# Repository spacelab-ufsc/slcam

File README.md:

<h1 align="center">
    SLCam
    <br>
</h1>

<h4 align="center">Camera payload designed and developed by SpaceLab.</h4>

<p align="center">

</p>

<p align="center">
    <a href="#overview">Overview</a> •
    <a href="#repository-organization">Repository Organizarion</a> •
    <a href="#releases">Releases</a> •
    <a href="#notes">Notes</a>
</p>

## Overview

The SLCam ("SpaceLab Camera") is a camera payload designed to be used in nanosatellite missions. The main object is to take pictures of the Earth from space. It's the first project from SpaceLab using cameras in payloads.

## Repository Organization

* docs: Technical documentation (including firmware, hardware, user guide, and datasheet).
* firmware: Firmware project (sources and configs).
* hardware: Hardware project (sources and outputs).
* mechanical: Mechanical project (sources and outputs).
* software: Software to communicate with the camera (sources).

## License

This project is open-source under three different licenses: GNU General Public License v3.0 for firmware sources, CERN Open Hardware License v2.0 for hardware and mechanical files, and CC BY-SA 4.0 for the documentation. Some third-part files and libraries are subjected to their specific terms and licenses.

## Releases

The SLCam software and hardware releases are synchronized in order to garantee compatibility. Then, using diferent versions might lead to unpredictable behavior. Refer to the [documentation](https://github.com/spacelab-ufsc/slcam/tree/main/doc) for compatibility notes.

## Notes

More info about the SpaceLab: [GitHub](https://github.com/spacelab-ufsc/spacelab) and [Website](https://spacelab.ufsc.br/en/home/).

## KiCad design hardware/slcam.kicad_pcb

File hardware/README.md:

<h1 align="center">
    SLCAM HARDWARE PROJECT
    <br>
</h1>

<h4 align="center">Hardware project of the SLCam module.</h4>

<p align="center">

</p>

<p align="center">
    <a href="#overview">Overview</a> •
    <a href="#bd">Block Diagram</a> •
    <a href="#license">License</a>
</p>

## Overview

The hardware project of the SpaceLab camera is composed by the PCB of the controller module.

## Block Diagram

The block diagram of the controller PCB can be seen below:

## License

This repository containing hardware files is licensed under CERN Open Hardware License, version 2.

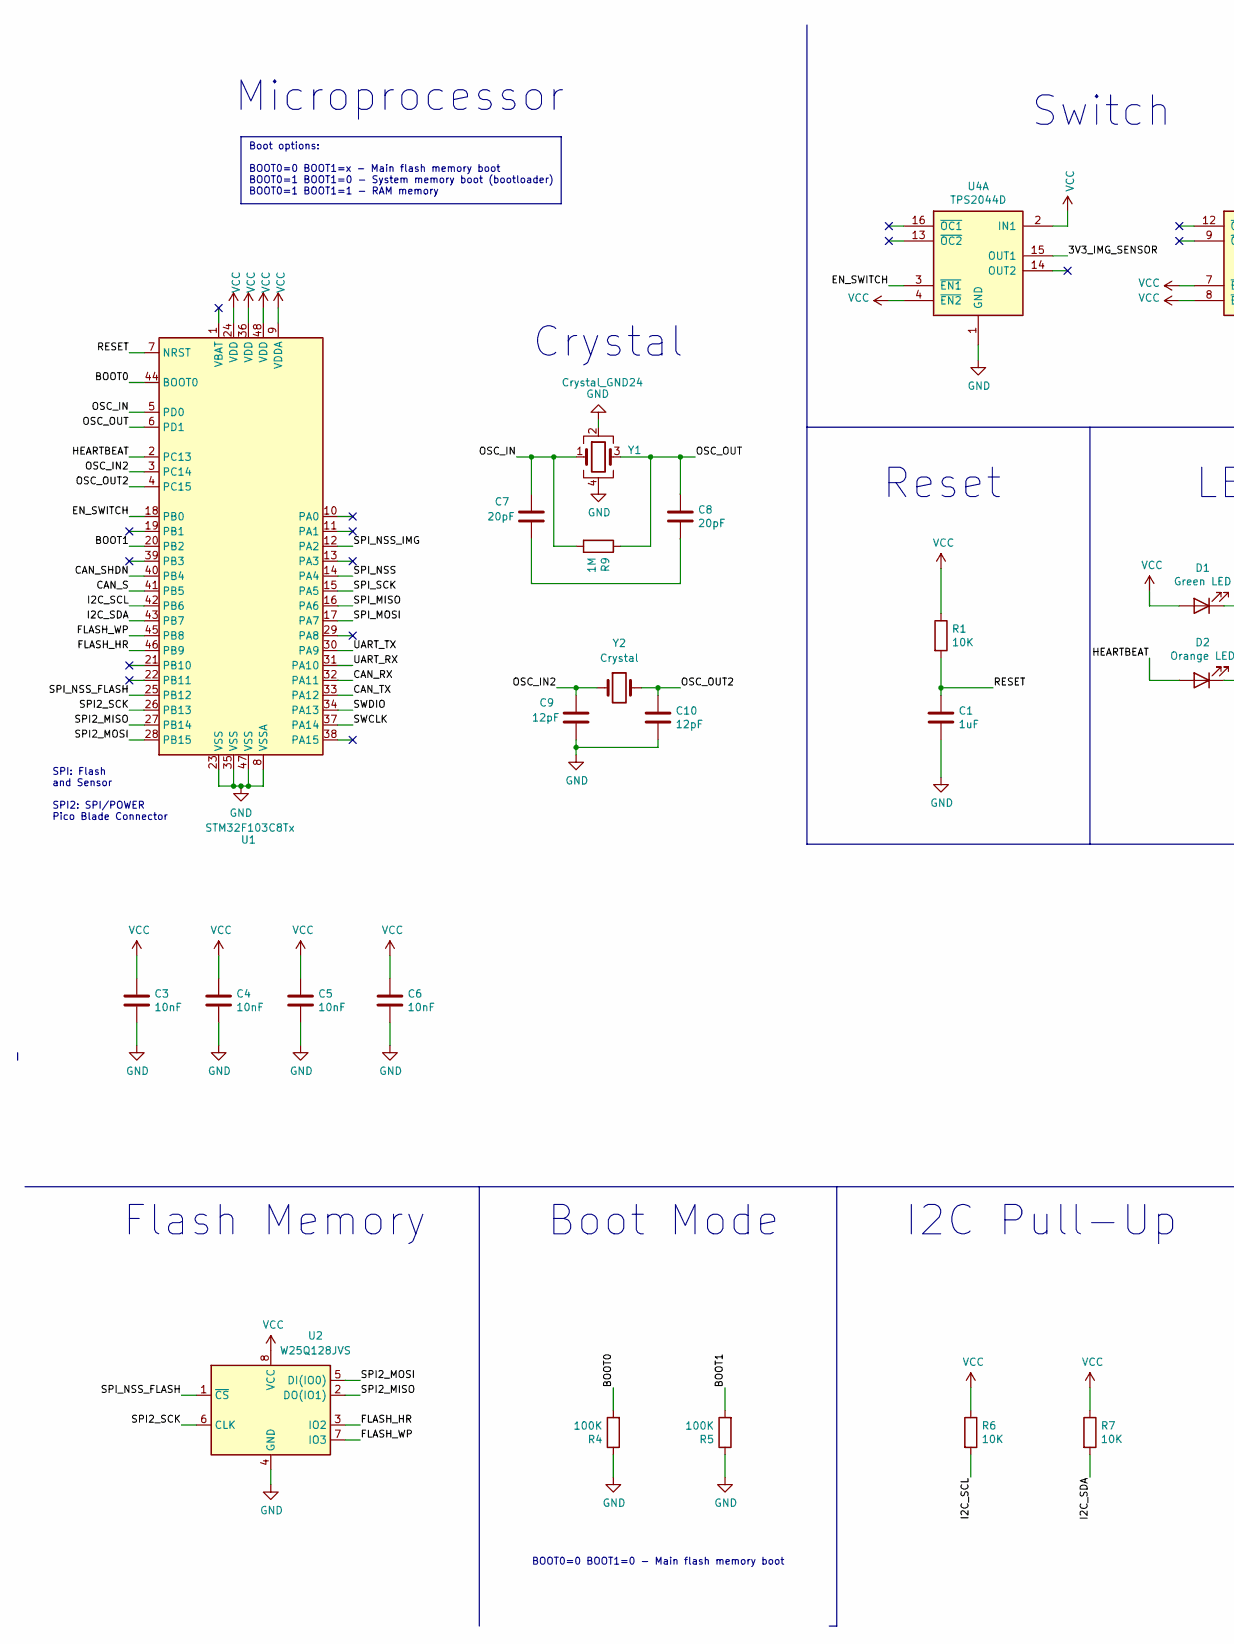
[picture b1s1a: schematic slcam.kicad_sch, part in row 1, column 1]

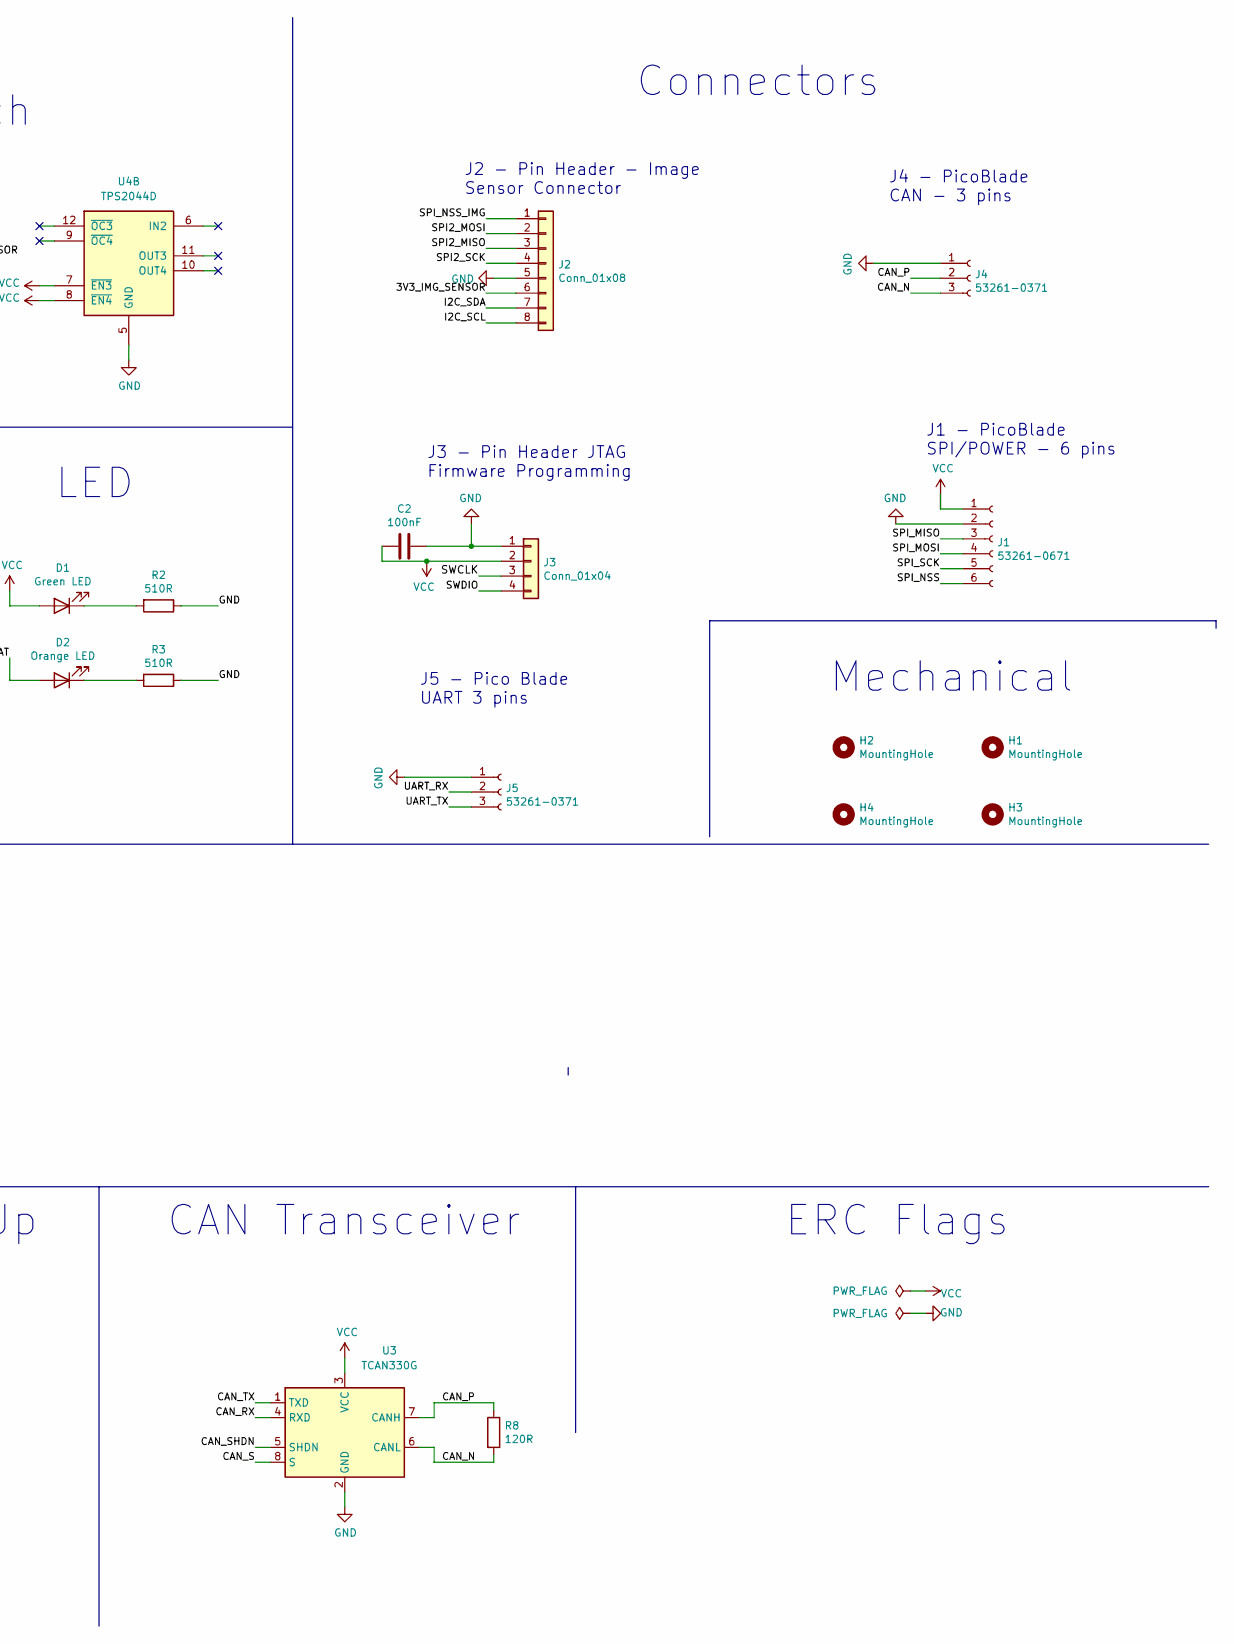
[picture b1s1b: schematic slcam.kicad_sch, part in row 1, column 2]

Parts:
C1: 1uF; C_0603_1608Metric_Pad1.05x0.95mm_HandSolder; Partnumber GCJ188R71E105KA01D
C2: 100nF; C_0603_1608Metric_Pad1.05x0.95mm_HandSolder; Partnumber C0603C104K5RAC3121
C3, C4, C5, C6: 10nF; C_0603_1608Metric_Pad1.05x0.95mm_HandSolder; Partnumber VJ0603Y103KXJAC31X
C7, C8: 20pF; C_0603_1608Metric_Pad1.05x0.95mm_HandSolder; Partnumber CBR06C200J5GACAUTO
C9, C10: 12pF; C_0603_1608Metric_Pad1.08x0.95mm_HandSolder; Partnumber CL21C120FBANNNC
D1: Green LED; LED_0603_1608Metric_Pad1.05x0.95mm_HandSolder; Partnumber 150060VS75003
D2: Orange LED; LED_0603_1608Metric_Pad1.05x0.95mm_HandSolder; Partnumber CSL1901DW1
H1, H2, H3, H4: MountingHole; MountingHole_3.2mm_M3_Pad
J1: 53261-0671; Molex_PicoBlade_53261-0671_1x06-1MP_P1.25mm_Horizontal; Partnumber 53261-0671
J2: Conn_01x08; PinHeader_1x08_P2.54mm_Vertical; Partnumber SSQ-108-03-G-S
J3: Conn_01x04; PinHeader_1x04_P2.54mm_Vertical; Partnumber 5-146305-4
J4, J5: 53261-0371; Molex_PicoBlade_53261-0371_1x03-1MP_P1.25mm_Horizontal; Partnumber 53261-0371
R1, R6, R7: 10K; R_0603_1608Metric_Pad1.05x0.95mm_HandSolder; Partnumber MCT06030C1002FP500
R2, R3: 510R; R_0603_1608Metric_Pad1.05x0.95mm_HandSolder; Partnumber MCT06030C5100FP500
R4, R5: 100K; R_0603_1608Metric_Pad1.05x0.95mm_HandSolder; Partnumber MCT0603MC1003FP500
R8: 120R; R_0603_1608Metric_Pad1.05x0.95mm_HandSolder; Partnumber MCT06030C1200FP500
R9: 1M; R_0603_1608Metric_Pad1.05x0.95mm_HandSolder; Partnumber MCT06030C1004FP500
U1: STM32F103C8Tx; LQFP-48_7x7mm_P0.5mm; Partnumber STM32F103C8T6
U2: W25Q128JVS; SOIC-8_5.23x5.23mm_P1.27mm; Partnumber W25Q128JVSIM TR
U3: TCAN330G; SOIC-8_3.9x4.9mm_P1.27mm; Partnumber TCAN330GD
U4: TPS2044D; SOIC-16_3.9x9.9mm_P1.27mm; Partnumber TPS2044D
Y1: Crystal_GND24; Crystal_SMD_Abracon_ABM8G-4Pin_3.2x2.5mm; Partnumber ECS-80-10-33-CHN-TR3
Y2: Crystal; Crystal_SMD_MicroCrystal_CC7V-T1A-2Pin_3.2x1.5mm_HandSolder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; Partnumber ECS-.327-12.5-34S-TR

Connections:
/3V3_IMG_SENSOR: J2.6, U4.15 (OUT1)
/BOOT0: R4.2, U1.44 (BOOT0)
/BOOT1: R5.2, U1.20 (PB2)
/CAN_N: J4.3, R8.2, U3.6 (CANL)
/CAN_P: J4.2, R8.1, U3.7 (CANH)
/CAN_RX: U1.32 (PA11), U3.4 (RXD)
/CAN_S: U1.41 (PB5), U3.8 (S)
/CAN_SHDN: U1.40 (PB4), U3.5 (SHDN)
/CAN_TX: U1.33 (PA12), U3.1 (TXD)
/EN_SWITCH: U1.18 (PB0), U4.3 (~EN1)
/FLASH_HR: U1.46 (PB9), U2.3 (IO2)
/FLASH_WP: U1.45 (PB8), U2.7 (IO3)
/HEARTBEAT: D2.2 (A), U1.2 (PC13)
/I2C_SCL: J2.8, R6.2, U1.42 (PB6)
/I2C_SDA: J2.7, R7.2, U1.43 (PB7)
/OSC_IN: C7.1, R9.2, U1.5 (PD0), Y1.1
/OSC_IN2: C9.1, U1.3 (PC14), Y2.1
/OSC_OUT: C8.1, R9.1, U1.6 (PD1), Y1.3
/OSC_OUT2: C10.1, U1.4 (PC15), Y2.2
/RESET: C1.1, R1.2, U1.7 (NRST)
/SPI2_MISO: J2.3, U1.27 (PB14), U2.2 (DO(IO1))
/SPI2_MOSI: J2.2, U1.28 (PB15), U2.5 (DI(IO0))
/SPI2_SCK: J2.4, U1.26 (PB13), U2.6 (CLK)
/SPI_MISO: J1.3, U1.16 (PA6)
/SPI_MOSI: J1.4, U1.17 (PA7)
/SPI_NSS: J1.6, U1.14 (PA4)
/SPI_NSS_FLASH: U1.25 (PB12), U2.1 (~CS)
/SPI_NSS_IMG: J2.1, U1.12 (PA2)
/SPI_SCK: J1.5, U1.15 (PA5)
/SWCLK: J3.3, U1.37 (PA14)
/SWDIO: J3.4, U1.34 (PA13)
/UART_RX: J5.2, U1.31 (PA10)
/UART_TX: J5.3, U1.30 (PA9)
GND: C1.2, C2.1, C3.2, C4.2, C5.2, C6.2, C9.2, C10.2, J1.2, J2.5, J3.1, J4.1, J5.1, R2.1, R3.1, R4.1, R5.1, U1.8 (VSSA), U1.23 (VSS), U1.35 (VSS), U1.47 (VSS), U2.4 (GND), U3.2 (GND), U4.1 (GND), U4.5 (GND), Y1.2, Y1.4
unnamed: C7.2, C8.2
unnamed: D1.1 (K), R2.2
unnamed: D2.1 (K), R3.2
VCC: C2.2, C3.1, C4.1, C5.1, C6.1, D1.2 (A), J1.1, J3.2, R1.1, R6.1, R7.1, U1.9 (VDDA), U1.24 (VDD), U1.36 (VDD), U1.48 (VDD), U2.8 (VCC), U3.3 (VCC), U4.2 (IN1), U4.4 (~EN2), U4.7 (~EN3), U4.8 (~EN4)

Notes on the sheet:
ERC Flags
Boot options: BOOT0=0 BOOT1=x - Main flash memory boot BOOT0=1 BOOT1=0 - System memory boot (bootloader) BOOT0=1 BOOT1=1 - RAM memory
Mechanical
J3 - Pin Header JTAG Firmware Programming
Switch
J1 - PicoBlade SPI/POWER - 6 pins
LED
J4 - PicoBlade CAN - 3 pins
Boot Mode
BOOT0=0 BOOT1=0 - Main flash memory boot
Connectors
J5 - Pico Blade UART 3 pins
J2 - Pin Header - Image Sensor Connector
Flash Memory
CAN Transceiver
SPI: Flash and Sensor SPI2: SPI/POWER Pico Blade Connector
Microprocessor
Reset
I2C Pull-Up
Crystal

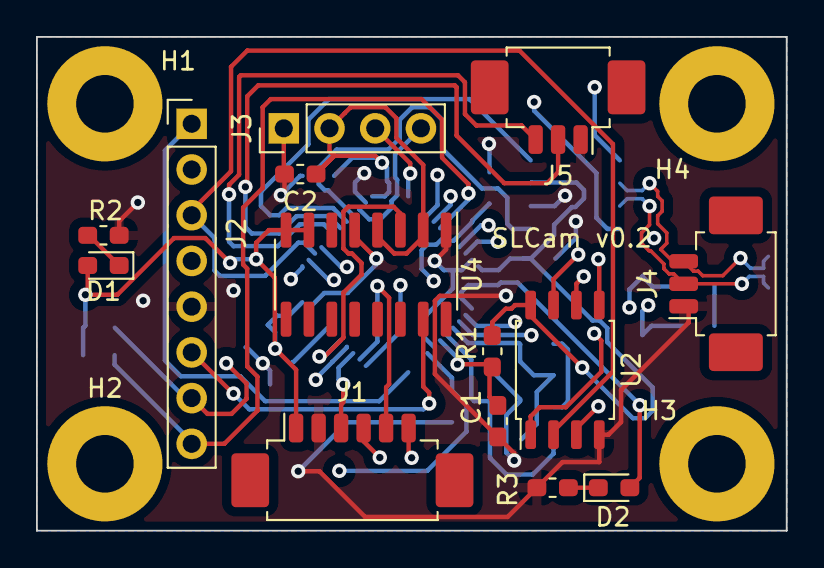
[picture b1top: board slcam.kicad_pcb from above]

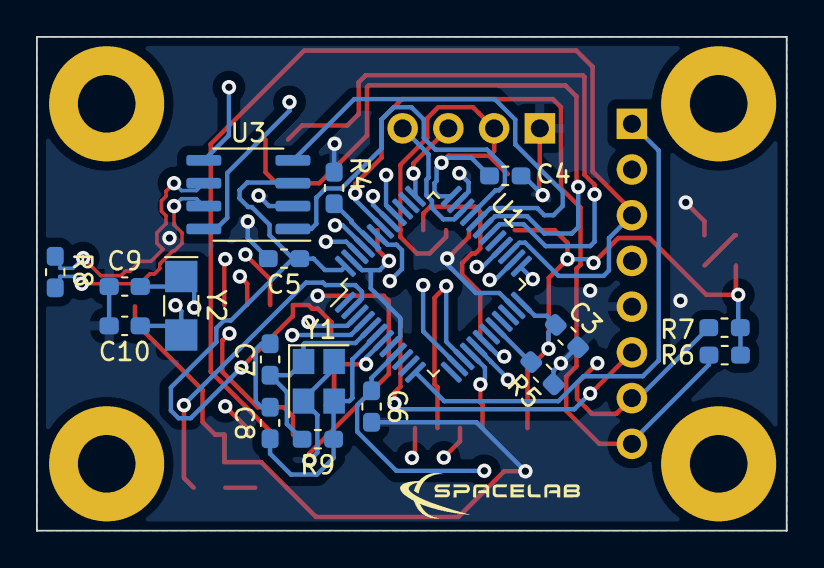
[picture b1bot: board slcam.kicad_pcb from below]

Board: 4 copper layers, 41.7 x 27.4 mm, 36 parts (18 on the bottom side), 38 nets.

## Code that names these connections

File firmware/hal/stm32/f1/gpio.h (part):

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/* Default alternate functions of some pins (with and without remapping) */

/* CAN1 / CAN GPIO */
#define GPIO_CAN1_RX			GPIO11		/* PA11 */
#define GPIO_CAN1_TX			GPIO12		/* PA12 */
#define GPIO_CAN_RX			GPIO_CAN1_RX	/* Alias */
#define GPIO_CAN_TX			GPIO_CAN1_TX	/* Alias */

#define GPIO_CAN_PB_RX			GPIO8		/* PB8 */
#define GPIO_CAN_PB_TX			GPIO9		/* PB9 */
#define GPIO_CAN1_PB_RX			GPIO_CAN_PB_RX	/* Alias */
#define GPIO_CAN1_PB_TX			GPIO_CAN_PB_TX	/* Alias */

#define GPIO_CAN_PD_RX			GPIO0		/* PD0 */
#define GPIO_CAN_PD_TX			GPIO1		/* PD1 */
#define GPIO_CAN1_PD_RX			GPIO_CAN_PD_RX	/* Alias */
#define GPIO_CAN1_PD_TX			GPIO_CAN_PD_TX	/* Alias */

/* CAN1 / CAN BANK */
#define GPIO_BANK_CAN1_RX		GPIOA		/* PA11 */
#define GPIO_BANK_CAN1_TX		GPIOA		/* PA12 */
#define GPIO_BANK_CAN_RX		GPIO_BANK_CAN1_RX /* Alias */
#define GPIO_BANK_CAN_TX		GPIO_BANK_CAN1_TX /* Alias */

#define GPIO_BANK_CAN_PB_RX		GPIOB		/* PB8 */
#define GPIO_BANK_CAN_PB_TX		GPIOB		/* PB9 */
#define GPIO_BANK_CAN1_PB_RX		GPIO_BANK_CAN_PB_RX /* Alias */
#define GPIO_BANK_CAN1_PB_TX		GPIO_BANK_CAN_PB_TX /* Alias */

#define GPIO_BANK_CAN_PD_RX		GPIOD		/* PD0 */
#define GPIO_BANK_CAN_PD_TX		GPIOD		/* PD1 */
#define GPIO_BANK_CAN1_PD_RX		GPIO_BANK_CAN_PD_RX /* Alias */
#define GPIO_BANK_CAN1_PD_TX		GPIO_BANK_CAN_PD_TX /* Alias */

/* CAN2 GPIO */
#define GPIO_CAN2_RX			GPIO12		/* PB12 */
#define GPIO_CAN2_TX			GPIO13		/* PB13 */

#define GPIO_CAN2_RE_RX			GPIO5		/* PB5 */
#define GPIO_CAN2_RE_TX			GPIO6		/* PB6 */

/* CAN2 BANK */
#define GPIO_BANK_CAN2_RX		GPIOB		/* PB12 */
#define GPIO_BANK_CAN2_TX		GPIOB		/* PB13 */

#define GPIO_BANK_CAN2_RE_RX		GPIOB		/* PB5 */
#define GPIO_BANK_CAN2_RE_TX		GPIOB		/* PB6 */

/* JTAG/SWD GPIO */
#define GPIO_JTMS_SWDIO			GPIO13		/* PA13 */
#define GPIO_JTCK_SWCLK			GPIO14		/* PA14 */
#define GPIO_JTDI			GPIO15		/* PA15 */
#define GPIO_JTDO_TRACESWO		GPIO3		/* PB3 */
#define GPIO_JNTRST			GPIO4		/* PB4 */
#define GPIO_TRACECK			GPIO2		/* PE2 */
#define GPIO_TRACED0			GPIO3		/* PE3 */
#define GPIO_TRACED1			GPIO4		/* PE4 */
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#define GPIO_TRACED3			GPIO6		/* PE6 */

/* JTAG/SWD BANK */
#define GPIO_BANK_JTMS_SWDIO		GPIOA		/* PA13 */
#define GPIO_BANK_JTCK_SWCLK		GPIOA		/* PA14 */
#define GPIO_BANK_JTDI			GPIOA		/* PA15 */
#define GPIO_BANK_JTDO_TRACESWO		GPIOB		/* PB3 */
#define GPIO_BANK_JNTRST		GPIOB		/* PB4 */
#define GPIO_BANK_TRACECK		GPIOE		/* PE2 */
#define GPIO_BANK_TRACED0		GPIOE		/* PE3 */
#define GPIO_BANK_TRACED1		GPIOE		/* PE4 */
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/* Timer5 GPIO */
#define GPIO_TIM5_CH1			GPIO0		/* PA0 */
#define GPIO_TIM5_CH2			GPIO1		/* PA1 */
#define GPIO_TIM5_CH3			GPIO2		/* PA2 */
#define GPIO_TIM5_CH4			GPIO3		/* PA3 */

/* Timer5 BANK */
#define GPIO_BANK_TIM5_CH1		GPIOA		/* PA0 */
#define GPIO_BANK_TIM5_CH2		GPIOA		/* PA1 */
#define GPIO_BANK_TIM5_CH3		GPIOA		/* PA2 */
#define GPIO_BANK_TIM5_CH4		GPIOA		/* PA3 */
#define GPIO_BANK_TIM5			GPIOA

/* Timer4 GPIO */
#define GPIO_TIM4_CH1			GPIO6		/* PB6 */
#define GPIO_TIM4_CH2			GPIO7		/* PB7 */
#define GPIO_TIM4_CH3			GPIO8		/* PB8 */
#define GPIO_TIM4_CH4			GPIO9		/* PB9 */

#define GPIO_TIM4_RE_CH1		GPIO12		/* PD12 */
#define GPIO_TIM4_RE_CH2		GPIO13		/* PD13 */
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#define GPIO_TIM4_RE_CH4		GPIO15		/* PD15 */

/* Timer4 BANK */
#define GPIO_BANK_TIM4_CH1		GPIOB		/* PB6 */
#define GPIO_BANK_TIM4_CH2		GPIOB		/* PB7 */
#define GPIO_BANK_TIM4_CH3		GPIOB		/* PB8 */
#define GPIO_BANK_TIM4_CH4		GPIOB		/* PB9 */
#define GPIO_BANK_TIM4			GPIOB

#define GPIO_BANK_TIM4_RE_CH1		GPIOD		/* PD12 */
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#define GPIO_BANK_TIM4_RE		GPIOD

/* Timer3 GPIO */
#define GPIO_TIM3_CH1			GPIO6		/* PA6 */
#define GPIO_TIM3_CH2			GPIO7		/* PA7 */
#define GPIO_TIM3_CH3			GPIO0		/* PB0 */
#define GPIO_TIM3_CH4			GPIO1		/* PB1 */

#define GPIO_TIM3_PR_CH1		GPIO4		/* PB4 */
#define GPIO_TIM3_PR_CH2		GPIO5		/* PB5 */
#define GPIO_TIM3_PR_CH3		GPIO0		/* PB0 */
#define GPIO_TIM3_PR_CH4		GPIO1		/* PB1 */

#define GPIO_TIM3_FR_CH1		GPIO6		/* PC6 */
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#define GPIO_TIM3_FR_CH4		GPIO9		/* PC9 */

/* Timer3 BANK */
#define GPIO_BANK_TIM3_CH1		GPIOA		/* PA6 */
#define GPIO_BANK_TIM3_CH2		GPIOA		/* PA7 */
#define GPIO_BANK_TIM3_CH3		GPIOB		/* PB0 */
#define GPIO_BANK_TIM3_CH4		GPIOB		/* PB1 */
#define GPIO_BANK_TIM3_CH12		GPIOA
#define GPIO_BANK_TIM3_CH34		GPIOB

#define GPIO_BANK_TIM3_PR_CH1		GPIOB		/* PB4 */
#define GPIO_BANK_TIM3_PR_CH2		GPIOB		/* PB5 */
#define GPIO_BANK_TIM3_PR_CH3		GPIOB		/* PB0 */
#define GPIO_BANK_TIM3_PR_CH4		GPIOB		/* PB1 */
#define GPIO_BANK_TIM3_PR		GPIOB

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/* Timer2 GPIO */
#define GPIO_TIM2_CH1_ETR		GPIO0		/* PA0 */
#define GPIO_TIM2_CH2			GPIO1		/* PA1 */
#define GPIO_TIM2_CH3			GPIO2		/* PA2 */
#define GPIO_TIM2_CH4			GPIO3		/* PA3 */

#define GPIO_TIM2_PR1_CH1_ETR		GPIO15		/* PA15 */
#define GPIO_TIM2_PR1_CH2		GPIO3		/* PB3 */
#define GPIO_TIM2_PR1_CH3		GPIO2		/* PA2 */
#define GPIO_TIM2_PR1_CH4		GPIO3		/* PA3 */

#define GPIO_TIM2_PR2_CH1_ETR		GPIO0		/* PA0 */
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/* Timer2 BANK */
#define GPIO_BANK_TIM2_CH1_ETR		GPIOA		/* PA0 */
#define GPIO_BANK_TIM2_CH2		GPIOA		/* PA1 */
#define GPIO_BANK_TIM2_CH3		GPIOA		/* PA2 */
#define GPIO_BANK_TIM2_CH4		GPIOA		/* PA3 */
#define GPIO_BANK_TIM2			GPIOA

#define GPIO_BANK_TIM2_PR1_CH1_ETR	GPIOA		/* PA15 */
#define GPIO_BANK_TIM2_PR1_CH2		GPIOB		/* PB3 */
#define GPIO_BANK_TIM2_PR1_CH3		GPIOA		/* PA2 */
#define GPIO_BANK_TIM2_PR1_CH4		GPIOA		/* PA3 */
#define GPIO_BANK_TIM2_PR1_CH134	GPIOA

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#define GPIO_BANK_TIM2_FR_CH234		GPIOB

/* Timer1 GPIO */
#define GPIO_TIM1_ETR			GPIO12		/* PA12 */
#define GPIO_TIM1_CH1			GPIO8		/* PA8 */
#define GPIO_TIM1_CH2			GPIO9		/* PA9 */
#define GPIO_TIM1_CH3			GPIO10		/* PA10 */
#define GPIO_TIM1_CH4			GPIO11		/* PA11 */
#define GPIO_TIM1_BKIN			GPIO12		/* PB12 */
#define GPIO_TIM1_CH1N			GPIO13		/* PB13 */
#define GPIO_TIM1_CH2N			GPIO14		/* PB14 */
#define GPIO_TIM1_CH3N			GPIO15		/* PB15 */

#define GPIO_TIM1_PR_ETR		GPIO12		/* PA12 */
#define GPIO_TIM1_PR_CH1		GPIO8		/* PA8 */
#define GPIO_TIM1_PR_CH2		GPIO9		/* PA9 */
#define GPIO_TIM1_PR_CH3		GPIO10		/* PA10 */
#define GPIO_TIM1_PR_CH4		GPIO11		/* PA11 */
#define GPIO_TIM1_PR_BKIN		GPIO6		/* PA6 */
#define GPIO_TIM1_PR_CH1N		GPIO7		/* PA7 */
#define GPIO_TIM1_PR_CH2N		GPIO0		/* PB0 */
#define GPIO_TIM1_PR_CH3N		GPIO1		/* PB1 */

#define GPIO_TIM1_FR_ETR		GPIO7		/* PE7 */
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#define GPIO_TIM1_FR_CH3N		GPIO12		/* PE12 */

/* Timer1 BANK */
#define GPIO_BANK_TIM1_ETR		GPIOA		/* PA12 */
#define GPIO_BANK_TIM1_CH1		GPIOA		/* PA8 */
#define GPIO_BANK_TIM1_CH2		GPIOA		/* PA9 */
#define GPIO_BANK_TIM1_CH3		GPIOA		/* PA10 */
#define GPIO_BANK_TIM1_CH4		GPIOA		/* PA11 */
#define GPIO_BANK_TIM1_BKIN		GPIOB		/* PB12 */
#define GPIO_BANK_TIM1_CH1N		GPIOB		/* PB13 */
#define GPIO_BANK_TIM1_CH2N		GPIOB		/* PB14 */
#define GPIO_BANK_TIM1_CH3N		GPIOB		/* PB15 */
#define GPIO_BANK_TIM1_ETR_CH1234	GPIOA
#define GPIO_BANK_TIM1_BKIN_CH123N	GPIOB

#define GPIO_BANK_TIM1_PR_ETR		GPIOA		/* PA12 */
#define GPIO_BANK_TIM1_PR_CH1		GPIOA		/* PA8 */
#define GPIO_BANK_TIM1_PR_CH2		GPIOA		/* PA9 */
#define GPIO_BANK_TIM1_PR_CH3		GPIOA		/* PA10 */
#define GPIO_BANK_TIM1_PR_CH4		GPIOA		/* PA11 */
#define GPIO_BANK_TIM1_PR_BKIN		GPIOA		/* PA6 */
#define GPIO_BANK_TIM1_PR_CH1N		GPIOA		/* PA7 */
#define GPIO_BANK_TIM1_PR_CH2N		GPIOB		/* PB0 */
#define GPIO_BANK_TIM1_PR_CH3N		GPIOB		/* PB1 */
#define GPIO_BANK_TIM1_PR_ETR_CH1234_BKIN_CH1N	GPIOA
#define GPIO_BANK_TIM1_PR_CH23N		GPIOB
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/* USART3 GPIO */
#define GPIO_USART3_TX			GPIO10		/* PB10 */
#define GPIO_USART3_RX			GPIO11		/* PB11 */
#define GPIO_USART3_CK			GPIO12		/* PB12 */
#define GPIO_USART3_CTS			GPIO13		/* PB13 */
#define GPIO_USART3_RTS			GPIO14		/* PB14 */

#define GPIO_USART3_PR_TX		GPIO10		/* PC10 */
#define GPIO_USART3_PR_RX		GPIO11		/* PC11 */
#define GPIO_USART3_PR_CK		GPIO12		/* PC12 */
#define GPIO_USART3_PR_CTS		GPIO13		/* PB13 */
#define GPIO_USART3_PR_RTS		GPIO14		/* PB14 */

#define GPIO_USART3_FR_TX		GPIO8		/* PD8 */
#define GPIO_USART3_FR_RX		GPIO9		/* PD9 */
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/* USART3 BANK */
#define GPIO_BANK_USART3_TX		GPIOB		/* PB10 */
#define GPIO_BANK_USART3_RX		GPIOB		/* PB11 */
#define GPIO_BANK_USART3_CK		GPIOB		/* PB12 */
#define GPIO_BANK_USART3_CTS		GPIOB		/* PB13 */
#define GPIO_BANK_USART3_RTS		GPIOB		/* PB14 */

#define GPIO_BANK_USART3_PR_TX		GPIOC		/* PC10 */
#define GPIO_BANK_USART3_PR_RX		GPIOC		/* PC11 */
#define GPIO_BANK_USART3_PR_CK		GPIOC		/* PC12 */
#define GPIO_BANK_USART3_PR_CTS		GPIOB		/* PB13 */
#define GPIO_BANK_USART3_PR_RTS		GPIOB		/* PB14 */

#define GPIO_BANK_USART3_FR_TX		GPIOD		/* PD8 */
#define GPIO_BANK_USART3_FR_RX		GPIOD		/* PD9 */
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/* USART2 GPIO */
#define GPIO_USART2_CTS			GPIO0		/* PA0 */
#define GPIO_USART2_RTS			GPIO1		/* PA1 */
#define GPIO_USART2_TX			GPIO2		/* PA2 */
#define GPIO_USART2_RX			GPIO3		/* PA3 */
#define GPIO_USART2_CK			GPIO4		/* PA4 */

#define GPIO_USART2_RE_CTS		GPIO3		/* PD3 */
#define GPIO_USART2_RE_RTS		GPIO4		/* PD4 */
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/* USART2 BANK */
#define GPIO_BANK_USART2_CTS		GPIOA		/* PA0 */
#define GPIO_BANK_USART2_RTS		GPIOA		/* PA1 */
#define GPIO_BANK_USART2_TX		GPIOA		/* PA2 */
#define GPIO_BANK_USART2_RX		GPIOA		/* PA3 */
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
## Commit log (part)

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2022-05-31 Initial project structure
2022-05-31 hardware: Adding a .gitignore for KiCAD projects
2022-05-31 hardware: Creating the KiCAD project
2022-06-02 Adding an initial block diagram of the hardware
2022-06-02 hardware: Initial BOM
2022-06-02 hardware: Minor fixes in the block diagram and BOM
2022-06-02 mechanical: Adding the STEP file of the ArduCam module
2022-07-02 docs: Initial content of the PDR presentation
2022-07-02 docs: pdr: Adding content to the slides and removing unnecessary files
2022-07-02 docs: pdr: Adding a .gitignore
2022-07-03 docs: pdr: Adding content to the slides
2022-07-05 Add previous camera CAD model and camera case CAD model
2022-07-05 add the previous camera_v2 CAD png
2022-07-08 Initial components placement #1 #4
2022-07-08 Initial layout
2022-07-11 firmware: Initial structure. closes #9
2022-07-11 firmware: Importing the FreeRTOS-LTS as a submodule #10
2022-07-11 firmware: Initial structure of the main Makefile
2022-07-14 General fixes #8 #9
2022-07-14 hardware: Adding exported 3D files
2022-07-20 docs: pdr: Final version
2022-08-14 firmware: Adding a linker script
2022-08-14 firmware: Compiling command in the Makefile
2022-08-14 firmware: Initial README file
2022-08-14 firmware: Release v0.1
2022-08-14 docs: pdr: Updating the README file #14
2022-08-19 mechanical: Renaming the mechanical project files following the organization standards. closes #16
2022-08-19 firmware: drivers: Initial structure of the OV2640 driver #22
2022-09-06 Developing schematics #11
2022-10-17 Fixing capacitors values and Crystal
2022-11-18 Initial layout and schematics fixes
2022-11-24 firmware: Changing compiler to c++ version
2022-12-01 firmware: Adding crt assembly file
2022-12-01 firmware: Including output files to gitignore
2022-12-01 firmware: Changing main to cpp file with blink example
2022-12-01 firmware: Adding crt.s to compilation
2022-12-01 Importing lib files from libopencm3 repo #27
2022-12-02 firmware: driver: Importing the w25qxx driver from LibDriver #31
2022-12-02 firmware: drivers: w25qxxx: Initial structure of the stm32f103 interface #31
2022-12-02 firmware: drivers: w25qxxx: Initial Makefile #31
2022-12-02 firmware: drivers: Including the compilation of the w25qxxx driver #31
2022-12-06 Hardware: Developing Layout #23
2022-12-08 firmware: hal: Initial Makefile structure for hal #27
2022-12-08 firmware: Removing main.c
2022-12-08 firmware: hal: Updating include directives #27
2022-12-09 firmware: Importing the original version of libopencm3 #27
2022-12-09 firmware: Updating the main Makefile #27
2022-12-09 firmware: Fixing the main file #27
2022-12-09 firmware: Temporally adding a C main file for tests #27
2022-12-09 firmware: Adding *.a files to .gitignore
2022-12-10 firmware: drivers: Updating the main header
2022-12-10 firmware: Updating the version number
2022-12-10 firmware: os: Importing FreeRTOS kernel v10.5.1 #10
2022-12-10 firmware: os: Adding a Makefile #10
2022-12-10 firmware: Initial FreeRTOS config file #10
2022-12-12 firmware: Preparing release v0.1.3
2022-12-26 Hardware: finishing layout, just missing footprints #23
2022-12-26 firmware: drivers: uart: Creating uart header and source files #43
2022-12-28 firmware: drivers: uart: Init uart function #43
2022-12-28 firmware: Adding uart driver to compilation #43
2022-12-29 firmware: drivers: uart: Returning int in initialization #43
2022-12-29 firmware: drivers: uart: Implementing send and receive byte functions #43
2022-12-29 firmware: libs: Importing containers lib #43
2022-12-30 firmware: libs: containers: Adding separe rules #43
2022-12-30 firmware: libs: containers: Fixing wrong pointer reference #43
2022-12-30 firmware: drivers: uart: Adding all function declarations #43
2023-01-03 firmware: config: Adding initial error codes #44
2023-01-05 firmware: Changing temporarily drivers rule #43
2023-01-10 hardware: fixing 3d models variable path
2023-01-23 hardware: Fixing the position of some labels in the layout #29
2023-01-23 hardware: Improving PCB tracks #29
2023-01-23 hardware: Fixing DRC warnings #29
2023-01-23 hardware: Updating KiCad version and minor fixes in the schematics #29
2023-01-23 hardware: Adding the project name/version and the SpaceLab logo to the PCB #23 #29 closes #38 closes #42
2023-01-23 hardware: Adding a table with info about the PCB to the layout project #29
2023-01-23 hardware: Adding renderizations of the PCB
2023-01-25 hardware: outputs: Updating the step model of the PCB
2023-01-25 hardware: Minor improvements in the schematics #28
2023-01-27 hardware: Adding the second part of the TPS2044D IC #28
2023-01-27 hardware: Updating the layout with the connections of the second part of the TPS2044D IC #28
2023-02-07 Adding a workflow to perform ERC and DRC on the hardware project (using KiBot)
2023-02-07 hardware: Adding the PWR_FLAG to remove ERC errors #28
2023-02-07 hardware: Updating the metadata of the schematics #28
2023-02-07 hardware: Updating the metadata of the layout and fixing DRC errors
2023-02-07 Disabling the PCB renderer in the PCB project workflow
2023-02-07 hardware: Removing unnecesssary files
2023-02-09 Updating the main README file. closes #3
2023-02-09 Adding missing libs
2023-02-09 General fixes and improvements #45 #46 #47 #47 #48 #49 #50 #51
2023-02-09 Adding a workflow to automatically build the latex documentation
2023-02-09 docs: Initial structure of the user manual
2023-02-11 hardware: fixing SPI pins #46
2023-02-11 hardware: fixing secong crystal schematics #45
2023-02-14 General fixes and improvements #45
2023-02-15 firmware: Adding stm32 family variable for opencm3 #24
2023-02-15 firmware: Removing unused main.cpp
2023-02-15 firmware: drivers: uart: Code improvements #43
2023-02-15 firmware: Adding libs to compilation chain #24
2023-02-15 firmware: drivers: uart: Queue uart functions with code optimizations #24
2023-02-16 firmware: config: Adding errno header file #44
2023-02-17 firmware: config: Adding metadata to the errno.h file #44
2023-02-28 firmware: drivers: uart: RX enable/disable implementation #43
2023-02-28 firmware: drivers: uart: Changing data to type uint16 accordingly to hal #43
2023-02-28 firmware: libs: containers: Changing data type to uint16
2023-02-28 firmware: drivers: uart: uart_write implementation #43
2023-02-28 firmware: config: Fixing formatting #44
2023-02-28 firmware: drivers: uart: Implementing error code handling #43
2023-03-03 hardware: finishing fixes and new components
2023-03-07 hardware: Fixing ERC errors
2023-03-07 hardware: Fixing DRC errors and general improvements in the layout
2023-03-08 hardware: Fixing the footprint of the 32 kHz crystal #45
2023-04-05 hardware: changing component values #52
2023-04-05 hardware: finished bill of materials #52
2023-04-05 docs: user_manual: Fixing the document title
2023-04-28 hardware: Removing bill of materials from README file
2023-04-28 hardware: schematics: Adding the partnumbers of some components #52
2023-04-29 hardware: schematics: Adding the partnumbers of components #52
2023-04-29 hardware: outputs: Updating the BOM. closes #52
2023-05-03 hardware: outputs: Updating the step model
2023-05-03 hardware: outputs: render: Updating the 3D renders
2023-05-03 hardware: outputs: Addding the exported gerber and centroid files. closes #30 closes 33
2023-05-08 hardware: updating BOM #30
2023-05-09 hardware: fixing mouting holes
2023-05-10 hardware: Fixing the partnumber of C3, C4, C5 and C6
2023-05-10 hardware: layout: Minor fixes
2023-05-10 hardware: outputs: Updating the 3D step model
2023-05-10 hardware: fixing mounting holes
2023-05-11 hardware: Fixing J2 position
2023-05-11 hardware: Fixing the boot mode option (changing to main flash memory)
2023-05-11 hardware: Fixing the value of some capacitors
2023-05-30 mechanical: Adding v0.2 step files
2023-05-31 mechanical: Adding the project files from solidworks
2023-05-31 firmware: changing version
2023-05-31 mechanical: outptus: Adding 3D rendered images
2023-05-31 mechanical: Adding technical drawnings
2023-06-02 mechanical: outputs: Adding PDF files of the technical drawings
2023-06-02 mechanical: Updating the README file
2023-06-02 Updating the main README file
2023-06-02 hardware: Updating the README file
2023-06-02 docs: user_manual: figures: Adding the block diagram drawing
2023-06-02 hardware: Fixing the README file
2023-06-02 docs: Removing old "figures" folder
2023-07-07 firmware: doc: Adding a product tree diagram
2023-07-07 firmware: Updating the README file
2023-07-12 firmware: drivers: uart: Fixing the code style and minor improvements #43
2023-07-12 firmware: drivers: uart: Minor improvements and adding doxygen documentation #43
2023-07-12 firmware: Updating the dependencies list
2023-07-20 firmware: importing i2c files from obdh2 #67
2023-07-20 firmware: deleting old functions implementation #67
2023-07-29 firmware: drivers: uart: Improving the Makefile script #43
2023-07-29 firmware: doc: Adding the TCAN33x driver to the product tree #73
2023-07-29 firmware: drivers: Initial structure of the CAN driver #72
2023-07-29 firmware: drivers: Adding the CAN driver to the Makefile #72
2023-07-29 firmware: tests: mockups: drivers: Initial structure of the CAN driver mockup #72
2023-08-02 firmware: drivers: can: Partial implementation of the CAN driver #72
2024-01-13 firmware: libs: containers: Fixing the queue and buffer libraries compilation to avoid conflicts with FreeRTOS
2024-01-13 firmware: Improving the main Makefile
2024-01-13 firmware: Fixing Makefiles for compiling the FreeRTOS
2024-01-13 firmware: system: Adding the implementation of the hook functions of FreeRTOS
2024-01-13 firmware: tasks: Adding a heartbeat task
2024-01-13 firmware: Creating tasks and starting scheduler in the main function
2024-01-14 firmware: system: Importing the sys_log module from the OBDH 2.0 project #74
2024-01-14 firmware: system: sys_log: Fixing and updating the Makefile #74
2024-01-14 firmware: system: sys_log: Updating the implementation #74
2024-01-17 firmware: system: sys_log: Updating the splash screen content #74
2024-01-17 firmware: tasks: Initial structure of the startup task
2024-01-17 firmware: Adding "-lm" as a linker flag #74
2024-01-17 firmware: config: Adding a flag to enable/disable the startup task
2024-01-22 firmware: Adding *.map files to .gitignore #17
2024-01-26 firmware: Decreasing the RAM sector length in the linker description
2024-01-26 firmware: system: Adding a function to configure the system clocks
2024-01-27 firmware: config: Fixing the FreeRTOS config. file
2024-01-27 firmware: Fixing the linker file
2024-02-01 firmware: libs: Importing libcsp v1.6 #75
2024-02-01 firmware: libs: libcsp-1.6: Adding an initial csp_autoconfig.h file #75
2024-02-01 firmware: libs: libcsp-1.6: Adding a Makefile. closes #75
2024-02-03 firmware: libs: Import the JSMN v1.1.0 library #77
2024-02-13 firmware: Updating the firmware version
2024-02-13 firmware: drivers: Initial structure of the SPI driver #69
2024-02-13 firmware: tests: mockups: drivers: Initial structure of the SPI wrap functions #69
2024-05-09 hardware: Defining the project license as CERN-OHL-2
2024-05-09 firmware: Updating the main README file with the project license notice
2024-05-09 mechanical: Defining the project license as CERN-OHL-2
2024-05-10 docs: pdr: Adding the license text file
2024-05-10 Updating the main README file with an overview text, and the project license notice
2024-06-11 firmware: Add "-mthumb","-mcpu=cortex-m3" and "-nostartfiles" to linker flags
2024-06-11 firmware: libs: libcsp-1.6: Fix csp_system and csp_time objects
2025-02-01 Create arquivo
2026-06-14 Update documentation
2026-06-20 docs: user_manual: Adding a drawing with the external dimensions of the mechanical case
2026-06-23 firmware: drivers: ov2640: Initial structure #22

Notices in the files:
firmware/hal/stm32/f1/gpio.h:
LGPL License Terms @ref lgpl_license
Copyright (C) 2009 Uwe Hermann <uwe@hermann-uwe.de>
Copyright (C) 2012 Piotr Esden-Tempski <piotr@esden.net>
Copyright (C) 2012 Ken Sarkies <ksarkies@internode.on.net>
This library is free software: you can redistribute it and/or modify
it under the terms of the GNU Lesser General Public License as published by
the Free Software Foundation, either version 3 of the License, or
(at your option) any later version.
hardware/README.md:
License: cern ohl 2
